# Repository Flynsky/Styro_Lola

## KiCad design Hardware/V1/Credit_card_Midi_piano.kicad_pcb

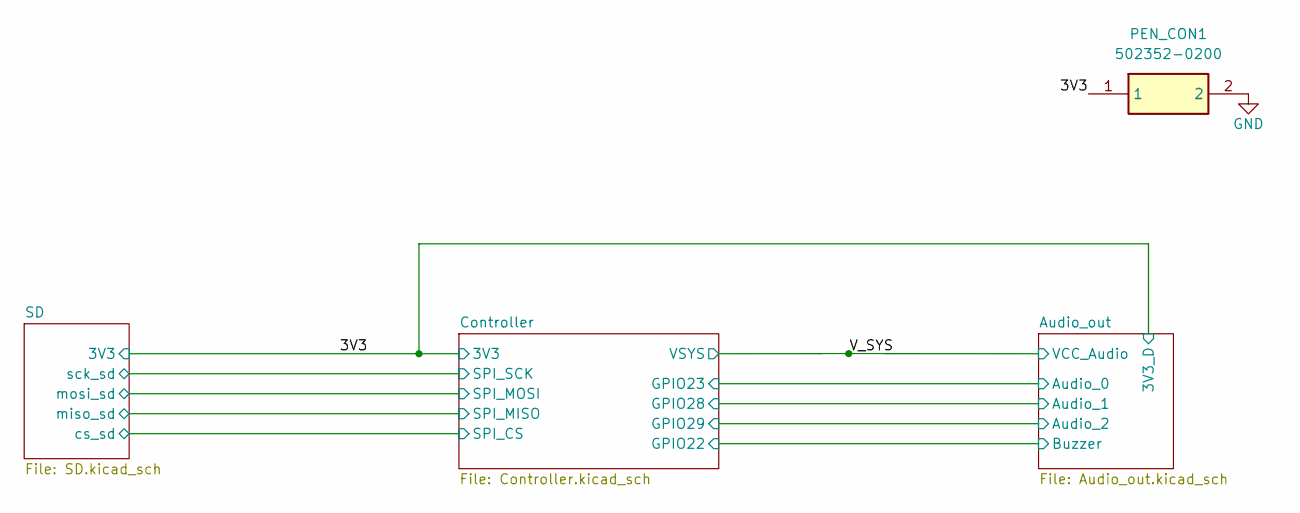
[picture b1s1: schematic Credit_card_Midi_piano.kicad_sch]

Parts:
PEN_CON1: 502352-0200; 5023520200; Mouser Part Number 538-502352-0200

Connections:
/3V3: PEN_CON1.1; also elsewhere on the board
GND: PEN_CON1.2; also elsewhere on the board

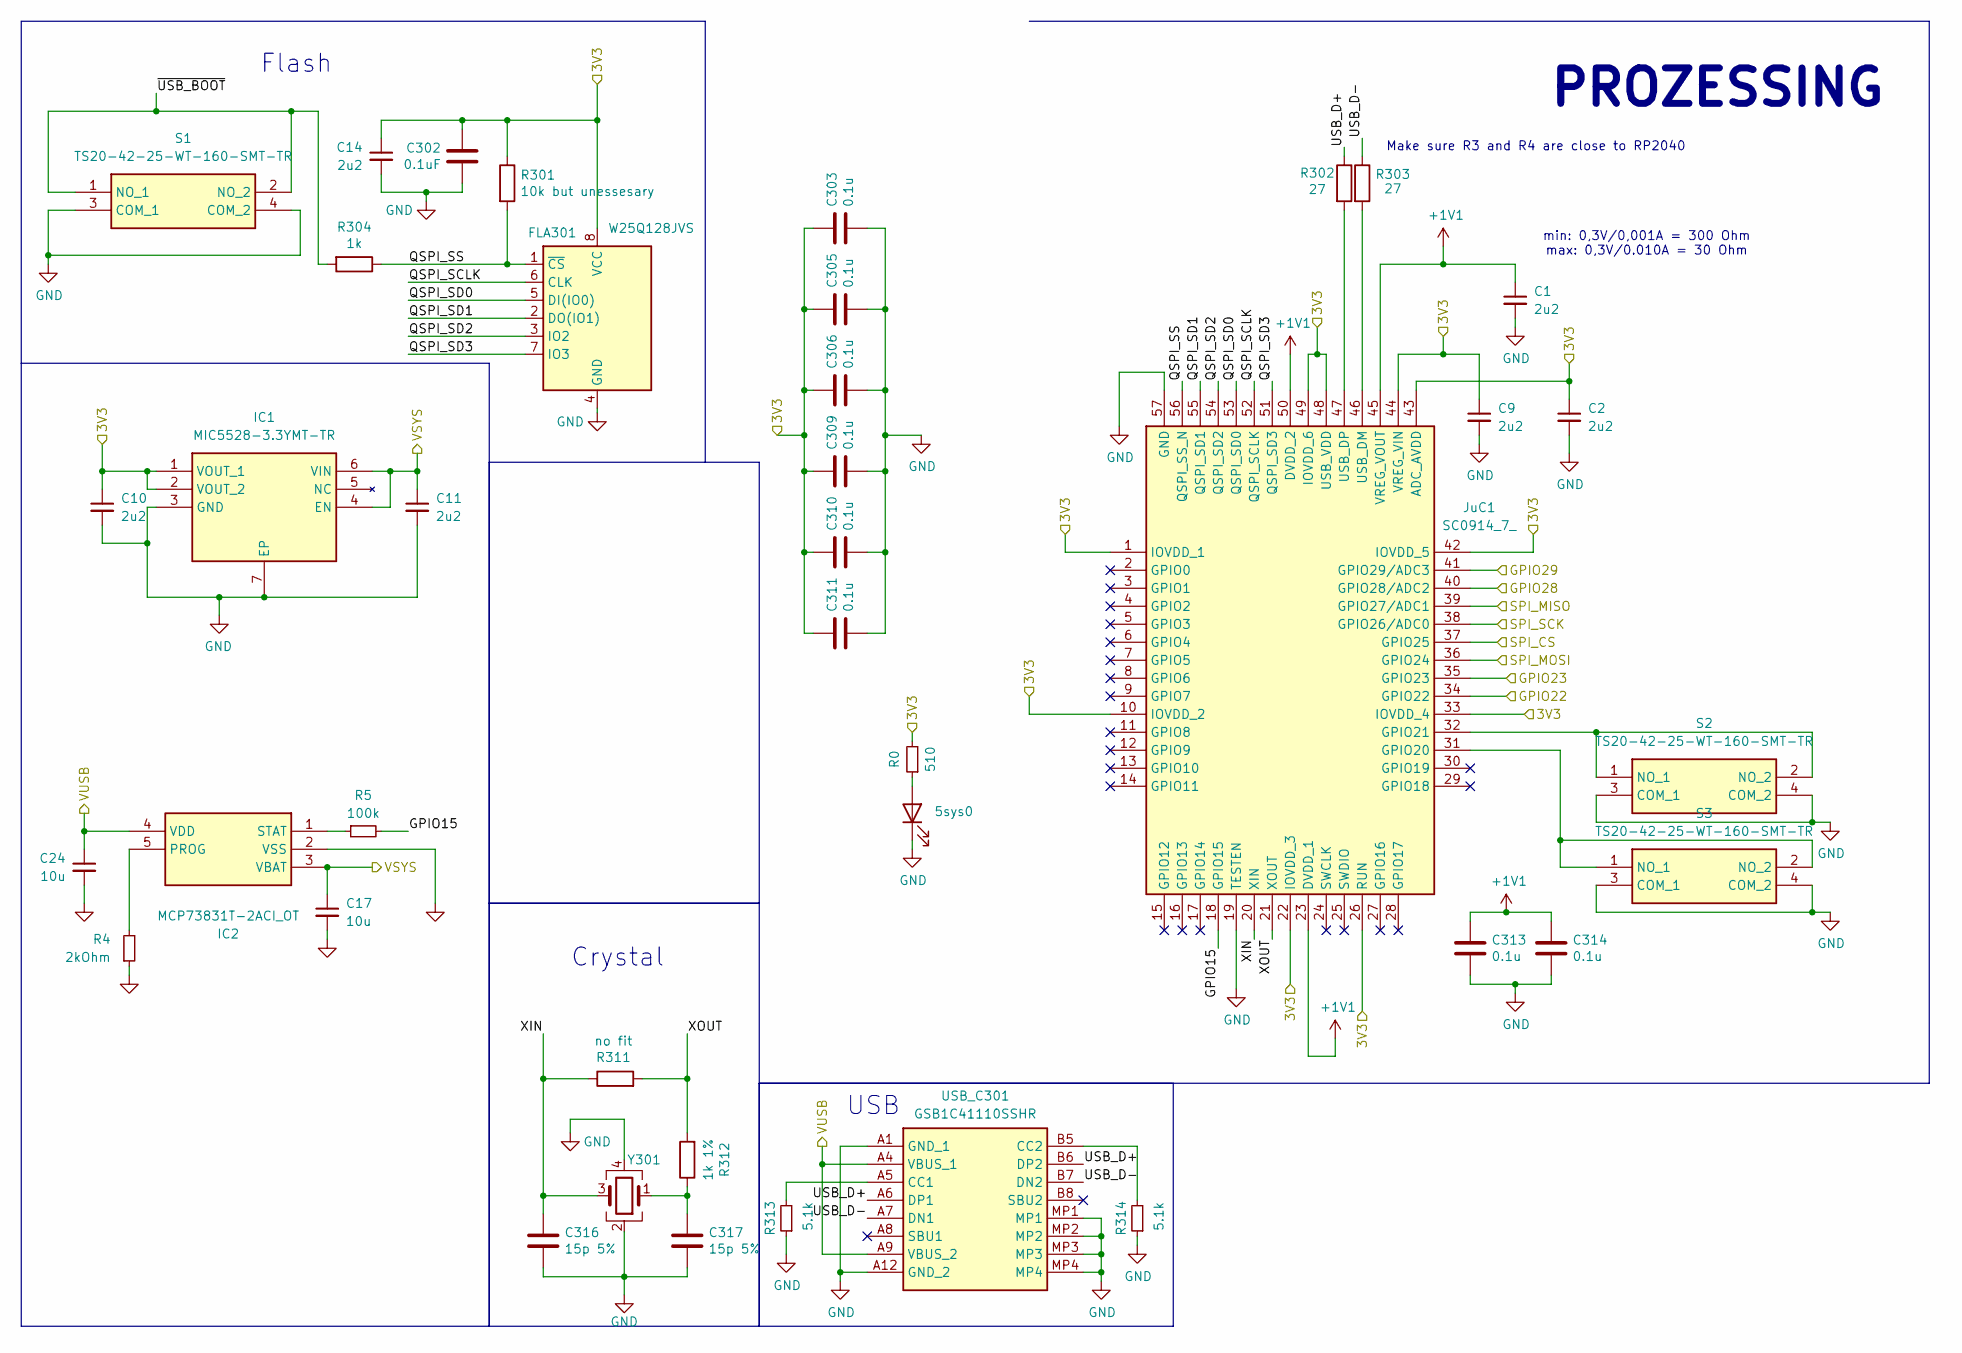
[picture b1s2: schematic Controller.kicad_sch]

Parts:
5sys0: APTD2012LCGCK; LEDC2012X120N; Mouser Part Number 604-APTD2012LCGCK
C1, C2, C9, C10, C11, C14: 2u2; CAPC1608X90N; Mouser Part Number 963-LMK107BJ225KA-T
C17, C24: 10u; CAPC1608X50N; Mouser Part Number 963-JMK107ABJ106MA-T
C302: 0.1uF; C_0402_1005Metric_Pad0.74x0.62mm_HandSolder
C303, C305, C306, C309, C310, C311, C313, C314: 0.1u; C_0402_1005Metric_Pad0.74x0.62mm_HandSolder
C316, C317: 15p 5%; C_0402_1005Metric_Pad0.74x0.62mm_HandSolder
FLA301: W25Q128JVS; SOIC127P790X216-8N
IC1: MIC5528-3.3YMT-TR; SON40P120X120X60-7N-D; Mouser Part Number 998-MIC5528-3.3YMTTR
IC2: MCP73831T-2ACI_OT; SOT95P270X145-5N; Mouser Part Number 579-MCP73831T-2ACIOT
JuC1: SC0914_7_; QFN40P700X700X90-57N-D; Mouser Part Number 358-SC09147
R0: 510; R_0603_1608Metric_Pad0.98x0.95mm_HandSolder
R4: 2kOhm; R_0603_1608Metric_Pad0.98x0.95mm_HandSolder
R5: 100k; R_0603_1608Metric_Pad0.98x0.95mm_HandSolder
R301: 10k but unessesary; R_0603_1608Metric_Pad0.98x0.95mm_HandSolder
R302, R303: 27; R_0603_1608Metric_Pad0.98x0.95mm_HandSolder
R304: 1k; R_0603_1608Metric_Pad0.98x0.95mm_HandSolder
R311: no fit; R_0402_1005Metric_Pad0.72x0.64mm_HandSolder
R312: 1k 1%; R_0603_1608Metric_Pad0.98x0.95mm_HandSolder
R313, R314: 5.1k; R_0603_1608Metric_Pad0.98x0.95mm_HandSolder
S1, S2, S3: TS20-42-25-WT-160-SMT-TR; TS204225WT160SMTTR; Mouser Part Number 179-TS204225WT160SMT
USB_C301: GSB1C41110SSHR; Manufacturer_Part_Number GSB1C41110SSHR
Y301: ABM8G-12.000MHZ-4Y-T3; ABM8G; Mouser Part Number 815-ABM8G-12-4YT3

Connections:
+1V1: C1.1, C313.1, C314.1, JuC1.23 (DVDD_1), JuC1.45 (VREG_VOUT), JuC1.50 (DVDD_2)
/3V3: C2.1, C9.1, C10.1, C14.1, C302.1, C303.1, C305.1, C306.1, C309.1, C310.1, C311.1, FLA301.8 (VCC), IC1.1 (VOUT_1), IC1.2 (VOUT_2), JuC1.1 (IOVDD_1), JuC1.10 (IOVDD_2), JuC1.22 (IOVDD_3), JuC1.26 (RUN), JuC1.33 (IOVDD_4), JuC1.42 (IOVDD_5), JuC1.43 (ADC_AVDD), JuC1.44 (VREG_VIN), JuC1.48 (USB_VDD), JuC1.49 (IOVDD_6), R0.2, R301.1; also elsewhere on the board
/Audio_out/Audio_0: JuC1.35 (GPIO23); also elsewhere on the board
/Audio_out/Audio_1: JuC1.40 (GPIO28/ADC2); also elsewhere on the board
/Audio_out/Audio_2: JuC1.41 (GPIO29/ADC3); also elsewhere on the board
/Audio_out/Buzzer: JuC1.34 (GPIO22); also elsewhere on the board
/Controller/GPIO15: JuC1.18 (GPIO15), R5.2
/Controller/QSPI_SCLK: FLA301.6 (CLK), JuC1.52 (QSPI_SCLK)
/Controller/QSPI_SD0: FLA301.5 (DI(IO0)), JuC1.53 (QSPI_SD0)
/Controller/QSPI_SD1: FLA301.2 (DO(IO1)), JuC1.55 (QSPI_SD1)
/Controller/QSPI_SD2: FLA301.3 (IO2), JuC1.54 (QSPI_SD2)
/Controller/QSPI_SD3: FLA301.7 (IO3), JuC1.51 (QSPI_SD3)
/Controller/QSPI_SS: FLA301.1 (~CS), JuC1.56 (QSPI_SS_N), R301.2, R304.1
/Controller/SPI_CS: JuC1.37 (GPIO25); also elsewhere on the board
/Controller/SPI_MISO: JuC1.39 (GPIO27/ADC1); also elsewhere on the board
/Controller/SPI_MOSI: JuC1.36 (GPIO24); also elsewhere on the board
/Controller/SPI_SCK: JuC1.38 (GPIO26/ADC0); also elsewhere on the board
/Controller/USB_D+: R302.1, USB_C301.A6 (DP1), USB_C301.B6 (DP2)
/Controller/USB_D-: R303.1, USB_C301.A7 (DN1), USB_C301.B7 (DN2)
/Controller/VUSB: C24.1, IC2.4 (VDD), USB_C301.A4 (VBUS_1), USB_C301.A9 (VBUS_2)
/Controller/XIN: C316.1, JuC1.20 (XIN), R311.1, Y301.3
/Controller/XOUT: JuC1.21 (XOUT), R311.2, R312.2
/Controller/~USB_BOOT: R304.2, S1.1 (NO_1), S1.2 (NO_2)
/V_SYS: C11.1, C17.1, IC1.4 (EN), IC1.6 (VIN), IC2.3 (VBAT); also elsewhere on the board
GND: 5sys0.1 (K), C1.2, C2.2, C9.2, C10.2, C11.2, C14.2, C17.2, C24.2, C302.2, C303.2, C305.2, C306.2, C309.2, C310.2, C311.2, C313.2, C314.2, C316.2, C317.2, FLA301.4 (GND), IC1.3 (GND), IC1.7 (EP), IC2.2 (VSS), JuC1.19 (TESTEN), JuC1.57 (GND), R4.1, R313.1, R314.1, S1.3 (COM_1), S1.4 (COM_2), S2.3 (COM_1), S2.4 (COM_2), S3.3 (COM_1), S3.4 (COM_2), USB_C301.A1 (GND_1), USB_C301.A12 (GND_2), USB_C301.MP1, USB_C301.MP2, USB_C301.MP3, USB_C301.MP4, Y301.2, Y301.4; also elsewhere on the board
unnamed: 5sys0.2 (A), R0.1
unnamed: C317.1, R312.1, Y301.1
unnamed: IC2.5 (PROG), R4.2
unnamed: IC2.1 (STAT), R5.1
unnamed: JuC1.31 (GPIO20), S3.1 (NO_1), S3.2 (NO_2)
unnamed: JuC1.32 (GPIO21), S2.1 (NO_1), S2.2 (NO_2)
unnamed: JuC1.46 (USB_DM), R303.2
unnamed: JuC1.47 (USB_DP), R302.2
unnamed: R313.2, USB_C301.A5 (CC1)
unnamed: R314.2, USB_C301.B5 (CC2)

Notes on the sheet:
min: 0,3V/0,001A = 300 Ohm max: 0,3V/0.010A = 30 Ohm
Crystal
Flash
USB
Make sure R3 and R4 are close to RP2040
PROZESSING

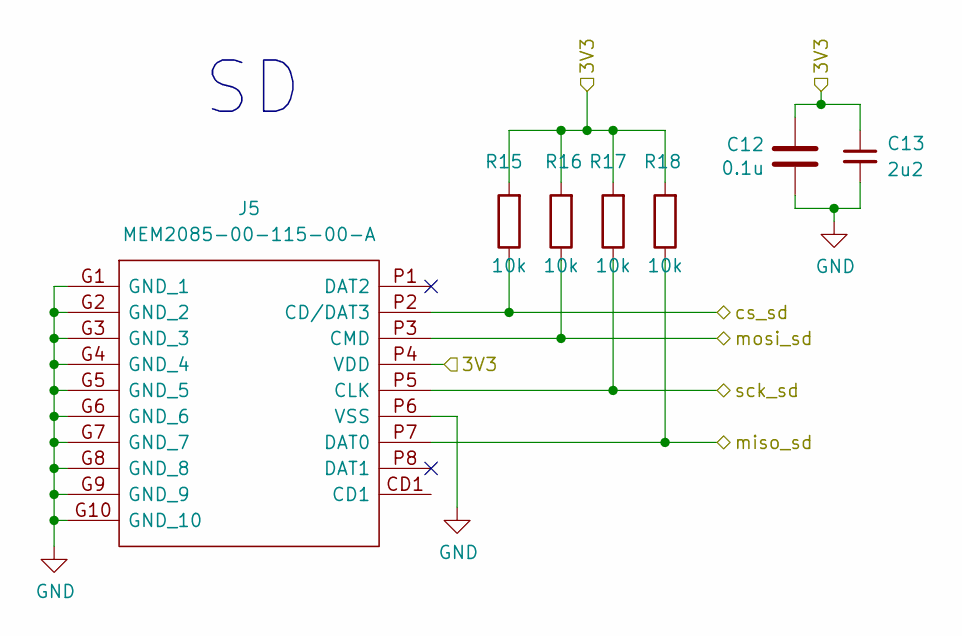
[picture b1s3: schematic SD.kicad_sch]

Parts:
C12: 0.1u; C_0402_1005Metric_Pad0.74x0.62mm_HandSolder
C13: 2u2; CAPC1608X90N; Mouser Part Number 963-LMK107BJ225KA-T
J5: MEM2085-00-115-00-A; MEM20850011500A; Mouser Part Number 640-MEM20850011500A
R15, R16, R17, R18: 10k; R_0603_1608Metric_Pad0.98x0.95mm_HandSolder

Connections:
/3V3: C12.1, C13.1, J5.P4 (VDD), R15.2, R16.2, R17.2, R18.2; also elsewhere on the board
/Controller/SPI_CS: J5.P2 (CD/DAT3), R15.1; also elsewhere on the board
/Controller/SPI_MISO: J5.P7 (DAT0), R18.1; also elsewhere on the board
/Controller/SPI_MOSI: J5.P3 (CMD), R16.1; also elsewhere on the board
/Controller/SPI_SCK: J5.P5 (CLK), R17.1; also elsewhere on the board
GND: C12.2, C13.2, J5.G1 (GND_1), J5.G2 (GND_2), J5.G3 (GND_3), J5.G4 (GND_4), J5.G5 (GND_5), J5.G6 (GND_6), J5.G7 (GND_7), J5.G8 (GND_8), J5.G9 (GND_9), J5.G10 (GND_10), J5.P6 (VSS); also elsewhere on the board

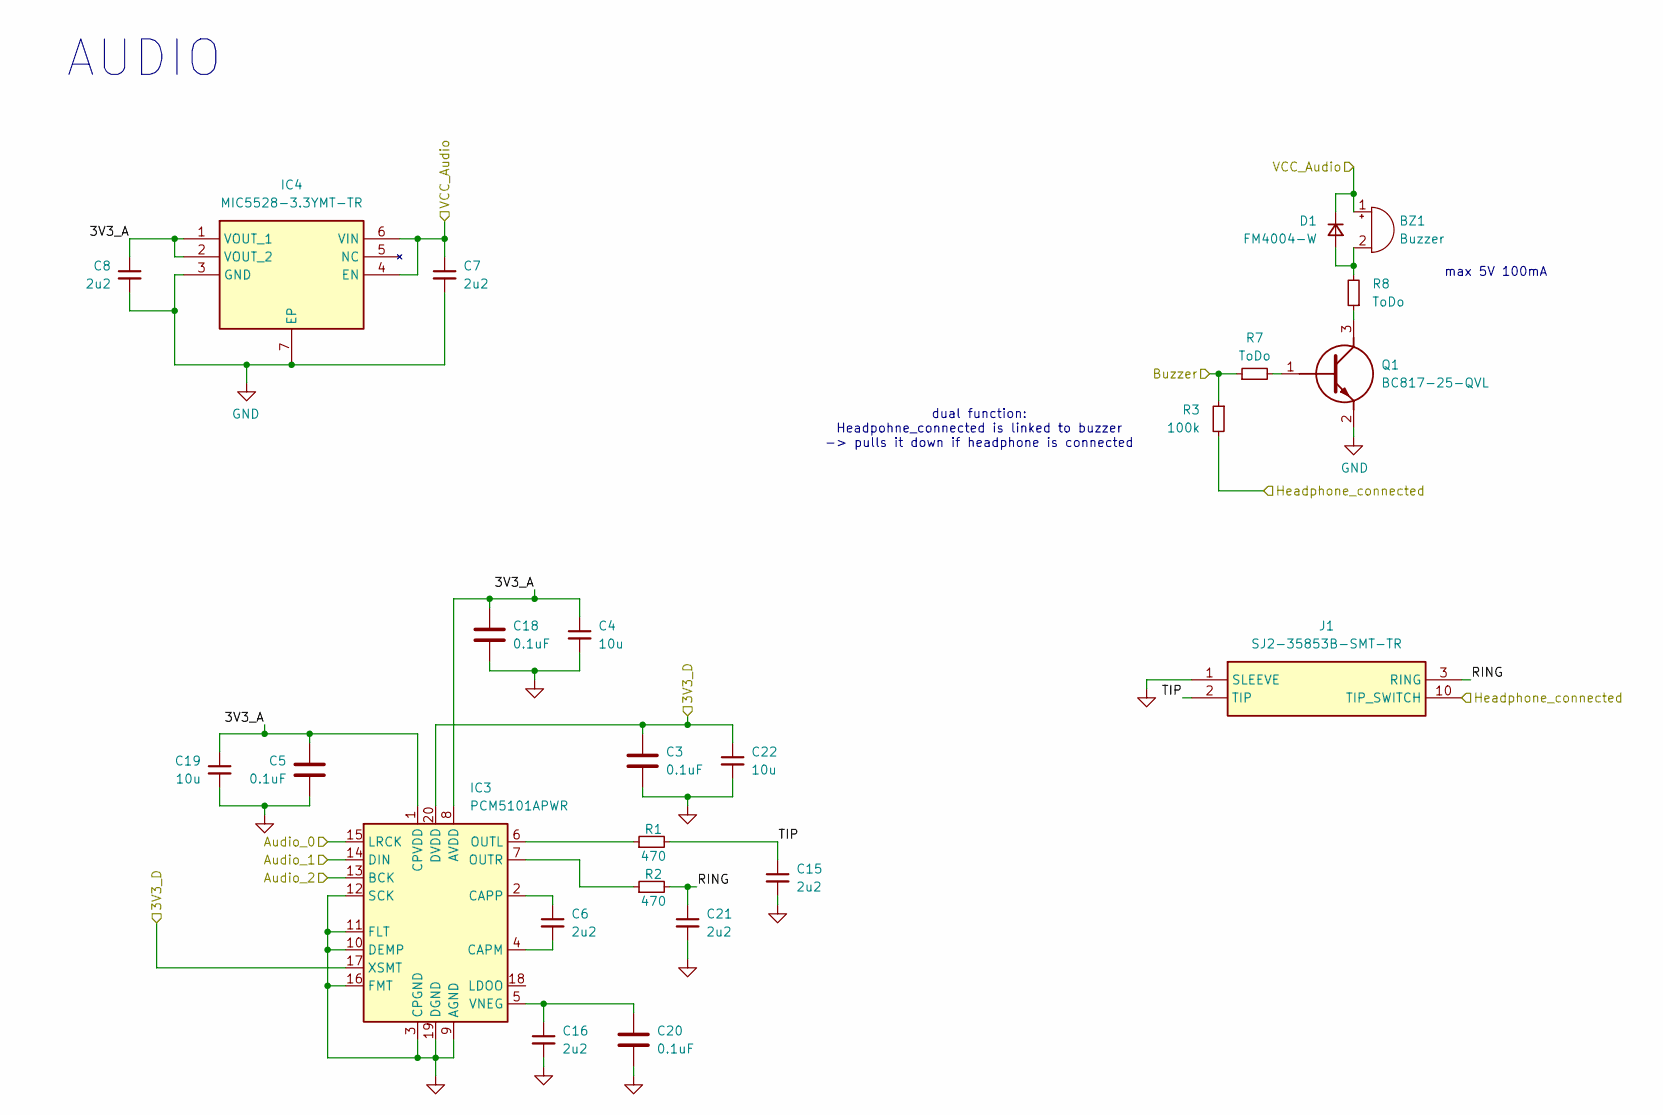
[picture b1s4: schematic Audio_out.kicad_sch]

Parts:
BZ1: Buzzer; CMT052575SMTTR
C3, C5, C18, C20: 0.1uF; C_0402_1005Metric_Pad0.74x0.62mm_HandSolder
C4, C19, C22: 10u; CAPC1608X50N; Mouser Part Number 963-JMK107ABJ106MA-T
C6, C7, C8, C15, C16, C21: 2u2; CAPC1608X90N; Mouser Part Number 963-LMK107BJ225KA-T
D1: FM4004-W; DIONM5025X231N; Mouser Part Number 583-FM4004
IC3: PCM5101APWR; TSSOP-20_4.4x6.5mm_P0.65mm; Mouser Part Number 595-PCM5101APWR
IC4: MIC5528-3.3YMT-TR; SON40P120X120X60-7N-D; Mouser Part Number 998-MIC5528-3.3YMTTR
J1: SJ2-35853B-SMT-TR; SJ235853BSMTTR; Mouser Part Number 490-SJ2-35853BSMT-TR
Q1: BC817-25-QVL; SOT95P230X110-3N; Mouser Part Number 771-BC817-25-QVL
R1, R2: 470; R_0603_1608Metric_Pad0.98x0.95mm_HandSolder
R3: 100k; R_0603_1608Metric
R7, R8: ToDo; R_0603_1608Metric

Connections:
/3V3: C3.2, C22.1, IC3.17 (XSMT), IC3.20 (DVDD); also elsewhere on the board
/Audio_out/3V3_A: C4.1, C5.2, C8.1, C18.2, C19.1, IC3.1 (CPVDD), IC3.8 (AVDD), IC4.1 (VOUT_1), IC4.2 (VOUT_2)
/Audio_out/Audio_0: IC3.15 (LRCK); also elsewhere on the board
/Audio_out/Audio_1: IC3.14 (DIN); also elsewhere on the board
/Audio_out/Audio_2: IC3.13 (BCK); also elsewhere on the board
/Audio_out/Buzzer: R3.1, R7.1; also elsewhere on the board
/Audio_out/Headphone_connected: J1.10 (TIP_SWITCH), R3.2
/Audio_out/RING: C21.1, J1.3 (RING), R2.2
/Audio_out/TIP: C15.1, J1.2 (TIP), R1.2
/V_SYS: BZ1.1 (+), C7.1, D1.1 (K), IC4.4 (EN), IC4.6 (VIN); also elsewhere on the board
GND: C3.1, C4.2, C5.1, C7.2, C8.2, C15.2, C16.2, C18.1, C19.2, C20.1, C21.2, C22.2, IC3.3 (CPGND), IC3.9 (AGND), IC3.10 (DEMP), IC3.11 (FLT), IC3.12 (SCK), IC3.16 (FMT), IC3.19 (DGND), IC4.3 (GND), IC4.7 (EP), J1.1 (SLEEVE), Q1.2 (E); also elsewhere on the board
unnamed: BZ1.2 (-), D1.2 (A), R8.2
unnamed: C6.2, IC3.4 (CAPM)
unnamed: C6.1, IC3.2 (CAPP)
unnamed: IC3.6 (OUTL), R1.1
unnamed: IC3.7 (OUTR), R2.1
unnamed: C16.1, C20.2, IC3.5 (VNEG)
unnamed: Q1.1 (B), R7.2
unnamed: Q1.3 (C), R8.1

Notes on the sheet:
AUDIO
dual function: Headpohne_connected is linked to buzzer -> pulls it down if headphone is connected
max 5V 100mA

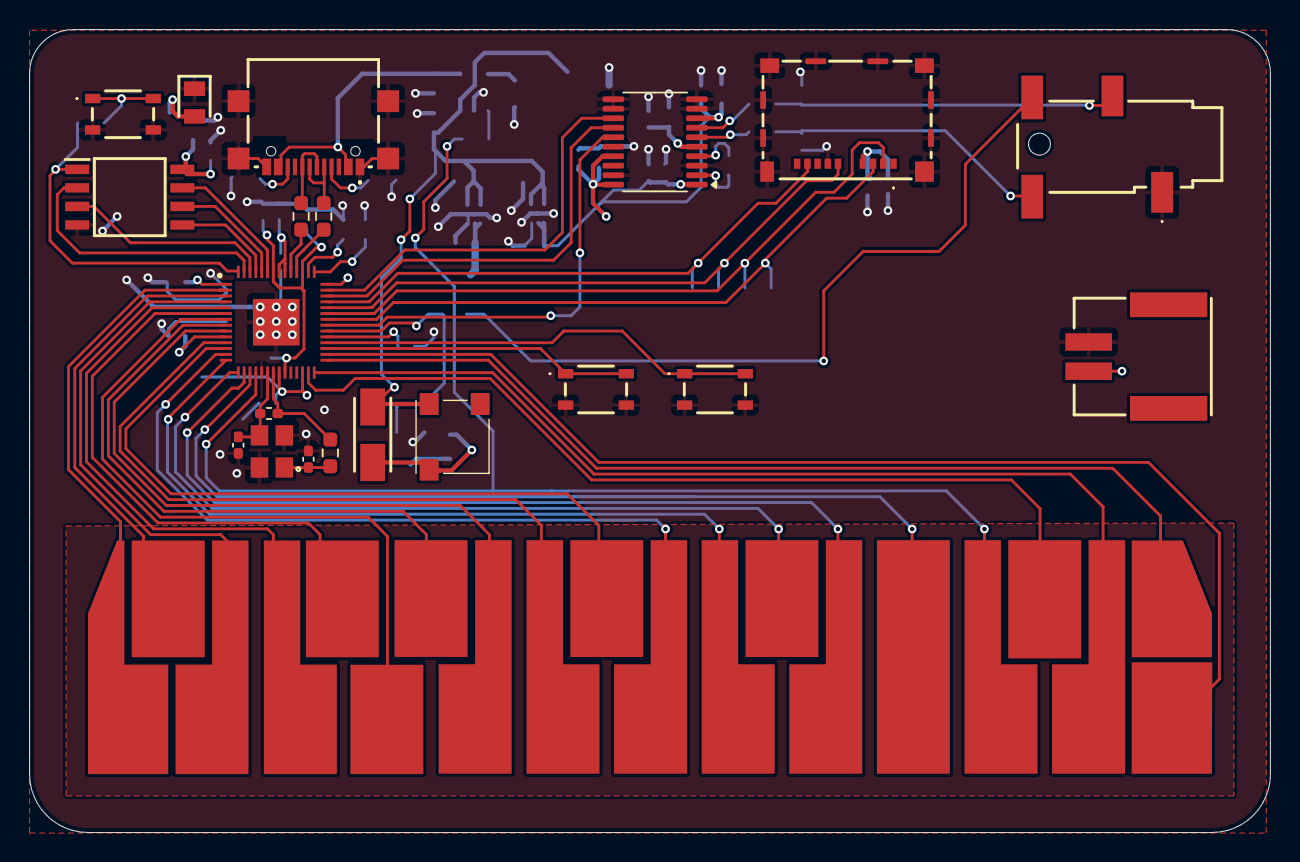
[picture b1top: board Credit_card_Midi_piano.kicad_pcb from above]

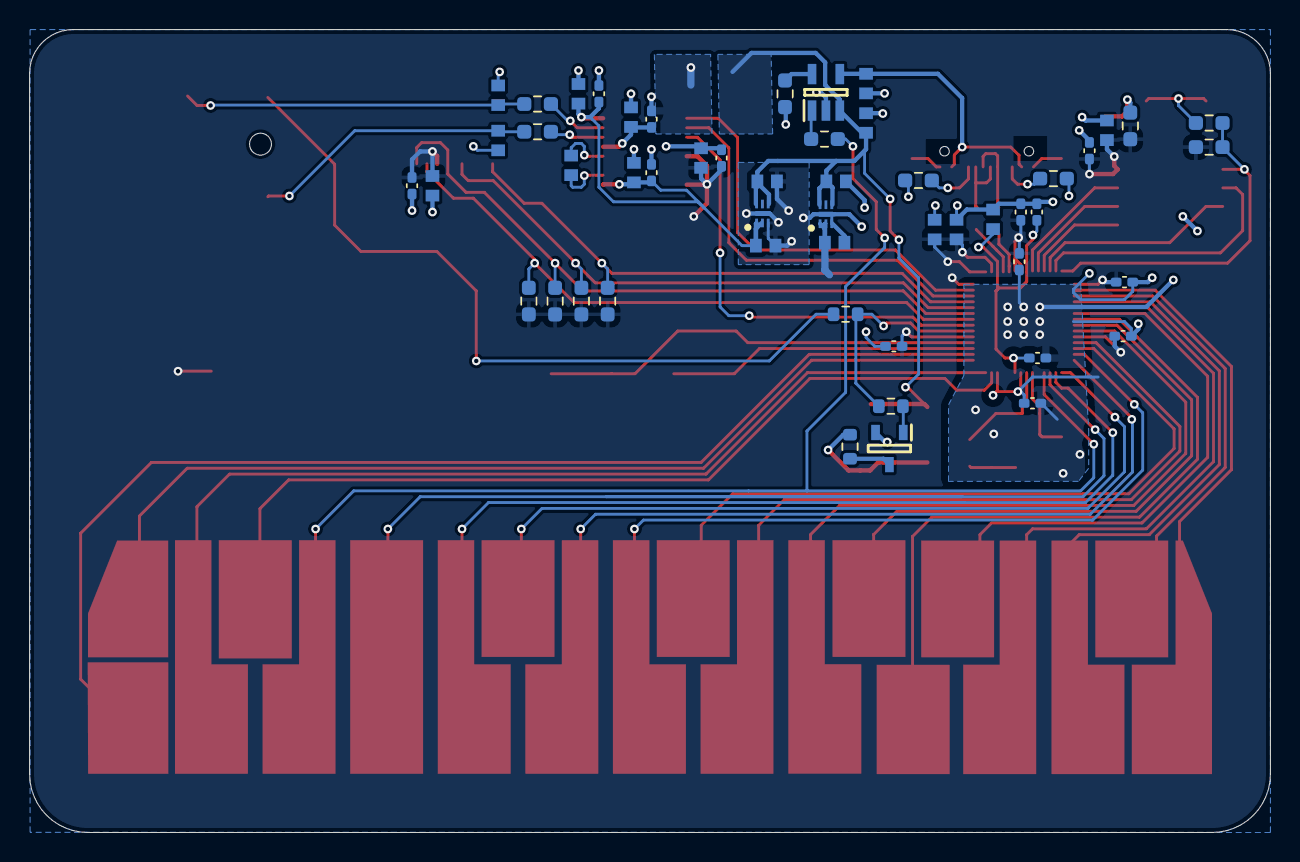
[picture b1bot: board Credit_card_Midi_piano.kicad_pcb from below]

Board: 2 copper layers, 85.0 x 55.0 mm, 72 parts (52 on the bottom side), 47 nets.

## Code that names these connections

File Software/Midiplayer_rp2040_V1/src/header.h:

/*-----------Header file for global defines, objekts, variables and functions-----------*/
#ifndef HEADER_H
#define HEADER_H

#include <Arduino.h>
/*--------Settings-----------------------*/
#define DEBUG_MODE 1    /*actrivates debug statements. 0=disable,1=Serial,2=TCP*/
#define COLOUR_SERIAL 1 /*activates/deactivates Serial.printing with color*/
#define USB_ENABLE 0    /*enables single drive USB functions*/
#define ADC_REF 3.0
#define ADC_RES 12 // ADC Resolution in Bit
#define ADC_MAX_READ (pow(2, ADC_RES) - 1)
const unsigned int ADC_MAX_WRITE = 100; //  Value where analogRrite = 100% duty cycle
const unsigned int ADC_FREQ_WRITE = 30000;

#define WATCHDOG_TIMEOUT 2000 // neds to be 8000ms max i think
#define CONNECTIONTIMEOUT 20  /*Conntection Timeout of the tcp client*/

extern unsigned long nMOTHERBOARD_BOOTUPS; // this number is stored in the flash and increses with every reset of th uC
/*----------------Pin mapping-------------*/
typedef enum
{
    PIN_FIRST_PAD = 0,
    nPAD = 16,
    PIN_PAD_TOP = 18,
    PIN_PAD_BOTTOM = 19,
    PIN_BUTTON_0 = 20,
    PIN_BUTTON_1 = 21,
    PIN_BUZZ = 22,
    PIN_HEADPHONE_CONNECT = 22,
    PIN_SD_MOSI = 24,
    PIN_SD_CS = 25,
    PIN_SD_SCK = 26,
    PIN_SD_MISO = 27,
    PIN_AUDIO_LRCK = 23, //Audio_0
    PIN_AUDIO_DIN = 28, //Audio_1
    PIN_AUDIO_BCK = 29 //Audio_2
} PIN_MAPPING;

uint32_t scan_keys();

#endif

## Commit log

2024-07-02 motherboard update
2024-07-03 added keys
2024-07-03 refined footprint
2024-07-18 changed to make boom better
2024-10-19 cleanup
2025-05-29 added html placer
2025-05-29 wirked on iS2
